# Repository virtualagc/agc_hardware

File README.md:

# AGC Hardware
This repository contains KiCAD projects and libraries for a replica of the Apollo Guidance Computer. The schematics have, for the most part, been digitized directly from [the original schematics](http://klabs.org/history/ech/agc_schematics/) for the computer. The schematics have been peppered with metadata required for digital simulation using my [agc\_simulation](https://github.com/thewonderidiot/agc_simulation) repository.

# Current Status
All logic modules (A1-A24) have been digitized and appear to be operating correctly in simulation. Additionally, one custom module, fixed\_erasable\_memory, has been designed. The simulation is able to completely pass the AGC Block Two Self-Check present in Aurora 12 (the only program we have so far with the complete version), so the central processor wiring is correct. Interfaces still need to be fully tested.

The current focus is on designing and building a working DSKY replica, which will make further interface testing significantly easier.

# Differences from the Real Thing
* Modern 74HC-series components are used due to the unavailability of RTL logic chips.
* I've taken advantage of the nearly-infinite fanout of 74HC chips to remove all fanout expansion gates.
* To reduce chip count, I've not limited myself to using only 3-input NOR gates; I also use NOT gates, 2-input NOR gates, and 4-input NOR gates, where applicable. Combined with the deletion of fanout expansion gates, the total chip count is roughly half of the original's.
* Again due to the nature of 74HC logic, outputs of NOR gates cannot be directly connected together as was possible with RTL. Where this is necessary (cross-module buses and >4 input gates), I've inserted fast open-drain buffers with accompanying pullup resistors. This gives very close to the same behavior, as the fan-in expander gates of the original were operating effectively open-collector lines.
* I've been fairly liberal about moving sections of logic around to make modules more stand-alone, and to condense related logic all into the same module. This facilited much easier development, and I anticipate it to make bench-testing individual modules easier when I've actually gotten boards manufactured. I also believe it to have significantly reduced the number of signals that will be going across the final backplane, although I have no numbers to back this up.
* The implementation for fixed and erasable memory module is custom, by me. It replaces all Tray B modules with the exception of the analog alarms module and the clock oscillator module.
* The implementation of the DSKY Indicator Driver module is the result of a joint reverse engineering effort between myself and Francois Rautenbach. It is based on several sources (R-700 volume III, Apollo 12 Mission Report, the CSM 104 Systems Handbook, the LM Systems Handbook, and the LM Primary Guidance Navigation and Control System Study Guide, among others). Thanks Francois!

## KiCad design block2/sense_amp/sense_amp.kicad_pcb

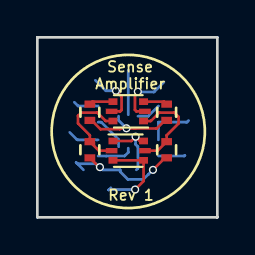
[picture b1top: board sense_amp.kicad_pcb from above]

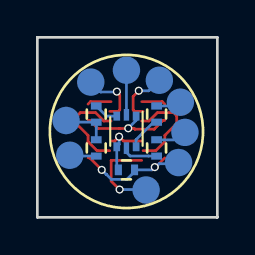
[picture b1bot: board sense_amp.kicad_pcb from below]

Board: 2 copper layers, 10.0 x 10.0 mm, 21 parts (15 on the bottom side), 18 nets.

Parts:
P1, P2, P3, P4, P6, P7, P8, P9, P10: CONN_01X01; Measurement_Point_Round-SMD-Pad_Small
Q1, Q3, Q5: DUAL_NPN_2; SOT-666
R1, R2, R7, R9: 5k; R_0402
R3, R4: 10; R_0402
R5, R6, R8: 250; R_0402

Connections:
unnamed: P1.1, Q5.3, Q5.4
unnamed: P2.1, Q1.2
unnamed: P3.1, R6.2
unnamed: P4.1, R5.2, R6.1
unnamed: P6.1, Q3.2
unnamed: P7.1, Q1.5
unnamed: P8.1, R8.2
unnamed: P9.1, R7.2
unnamed: P10.1, R1.1, R2.1, R9.1
unnamed: Q1.1, Q5.5, R1.2
unnamed: Q1.3, R3.1
unnamed: Q1.4, R4.1
unnamed: Q1.6, Q5.2, R2.2
unnamed: Q3.1, R3.2, R4.2
unnamed: Q3.3, R5.1
unnamed: Q3.4, Q5.1, Q5.6, R9.2
unnamed: Q3.5, R7.1
unnamed: Q3.6, R8.1

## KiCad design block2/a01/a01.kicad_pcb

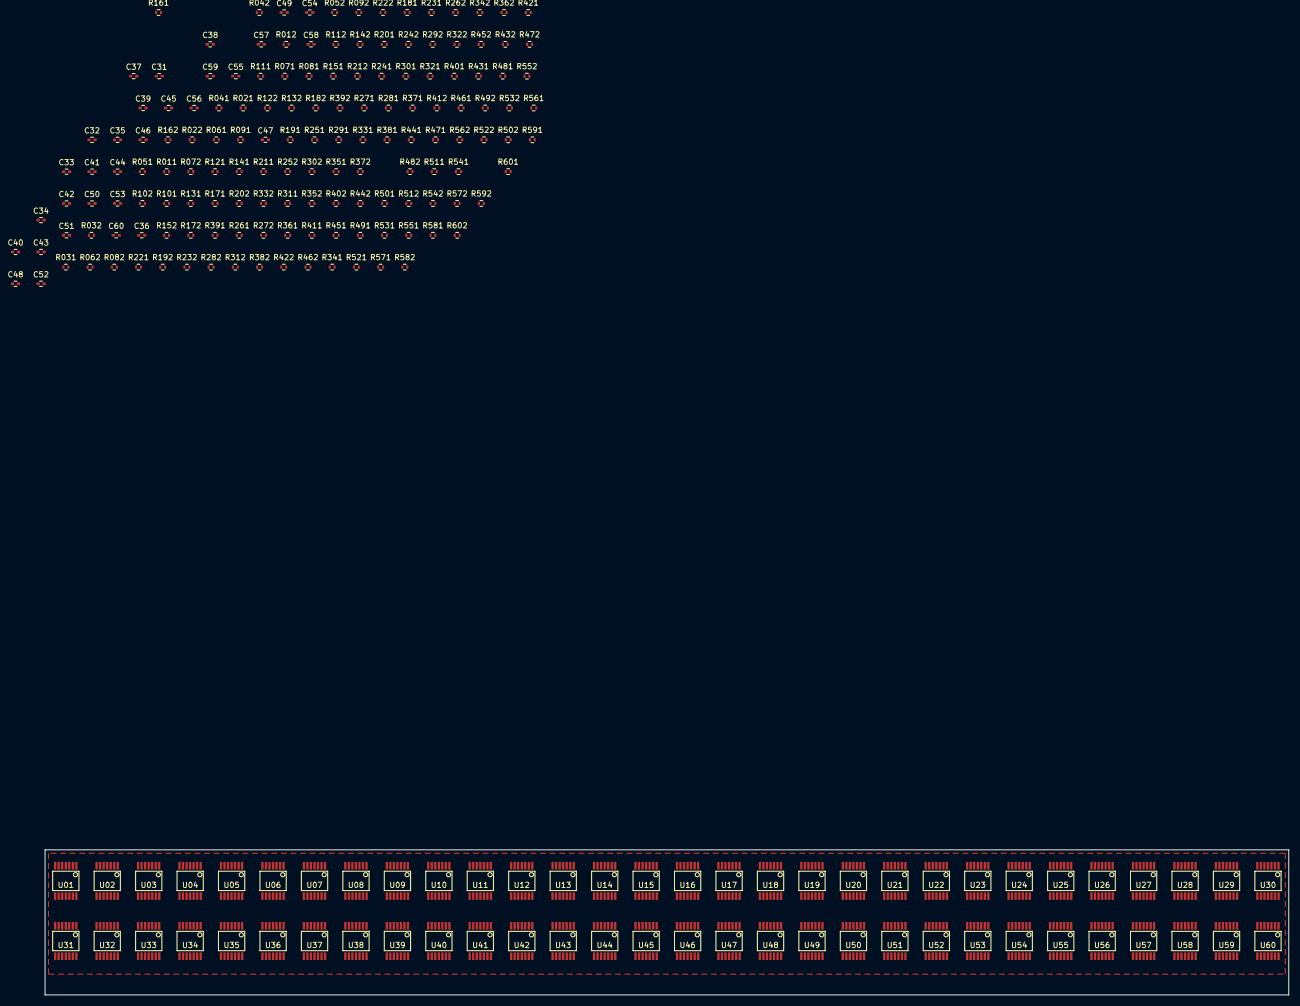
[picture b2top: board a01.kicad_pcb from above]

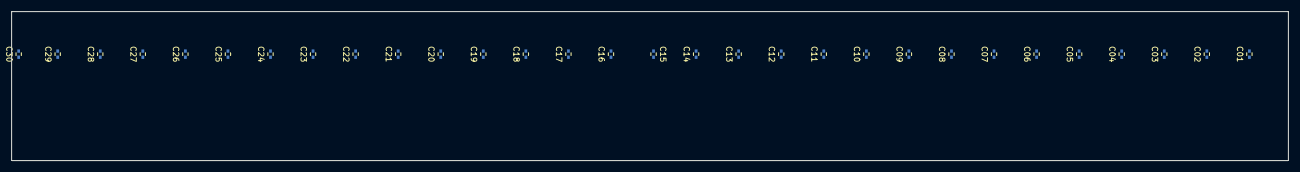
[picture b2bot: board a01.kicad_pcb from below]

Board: 2 copper layers, 228.6 x 26.7 mm, 240 parts (30 on the bottom side), 133 nets, no tracks yet.

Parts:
C01, C02, C03, C04, C05, C06, C07, C08, C09, C10, C11, C12, C13, C14, C15, C16, C17, C18, C19, C20, C21, C22, C23, C24, C25, C26, C27, C28, C29, C30, C31, C32, C33, C34, C35, C36, C37, C38, C39, C40, C41, C42, C43, C44, C45, C46, C47, C48, C49, C50, C51, C52, C53, C54, C55, C56, C57, C58, C59, C60: 0.1uF; C_0402
R011, R012, R021, R022, R031, R032, R041, R042, R051, R052, R061, R062, R071, R072, R081, R082, R091, R092, R101, R102, R111, R112, R121, R122, R131, R132, R141, R142, R151, R152, R161, R162, R171, R172, R181, R182, R191, R192, R201, R202, R211, R212, R221, R222, R231, R232, R241, R242, R251, R252, R261, R262, R271, R272, R281, R282, R291, R292, R301, R302, R311, R312, R321, R322, R331, R332, R341, R342, R351, R352, R361, R362, R371, R372, R381, R382, R391, R392, R401, R402, R411, R412, R421, R422, R431, R432, R441, R442, R451, R452, R461, R462, R471, R472, R481, R482, R491, R492, R501, R502, R511, R512, R521, R522, R531, R532, R541, R542, R551, R552, R561, R562, R571, R572, R581, R582, R591, R592, R601, R602: 3.3k; R_0402
U01, U02, U05, U06, U09, U13, U16, U20, U23, U27, U34, U35, U36, U38, U39, U41, U42, U43, U45, U48, U49, U52, U55, U56, U59, U60: 74HC05-B_C-E_F; SSOP-14
U03, U04, U07, U08, U18, U28, U29, U50, U54: 74HC05-ABC-E_F; SSOP-14
U10, U14, U17, U21: 74HC05-ACB-E_F; SSOP-14
U11, U15, U22, U46, U47, U51, U53, U57, U58: 74HC05-BAC-E_F; SSOP-14
U12, U19, U26: 74HC05-A_B-E_F; SSOP-14
U24: 74HC05-A_C-E_F; SSOP-14
U25, U44: 74HC05-ABC-DFE; SSOP-14
U30, U31: 74HC05-SPARE; SSOP-14
U32, U33: 74HC05-B_C-EDF; SSOP-14
U37, U40: 74HC05-BAC-DEF; SSOP-14

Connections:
0VDCA: C01.2, C02.2, C03.2, C04.2, C05.2, C06.2, C07.2, C08.2, C09.2, C10.2, C11.2, C12.2, C13.2, C14.2, C15.2, C16.2, C17.2, C18.2, C19.2, C20.2, C21.2, C22.2, C23.2, C24.2, C25.2, C26.2, C27.2, C28.2, C29.2, C30.2, C31.2, C32.2, C33.2, C34.2, C35.2, C36.2, C37.2, C38.2, C39.2, C40.2, C41.2, C42.2, C43.2, C44.2, C45.2, C46.2, C47.2, C48.2, C49.2, C50.2, C51.2, C52.2, C53.2, C54.2, C55.2, C56.2, C57.2, C58.2, C59.2, C60.2, U01.5, U01.7, U01.9, U02.5, U02.7, U02.9, U03.7, U03.9, U04.7, U04.9, U05.5, U05.7, U05.9, U06.5, U06.7, U06.9, U07.7, U07.9, U08.7, U08.9, U09.5, U09.7, U09.9, U10.7, U10.9, U11.7, U11.9, U12.1, U12.7, U12.9, U13.5, U13.7, U13.9, U14.7, U14.9, U15.7, U15.9, U16.5, U16.7, U16.9, U17.7, U17.9, U18.7, U18.9, U19.1, U19.7, U19.9, U20.5, U20.7, U20.9, U21.7, U21.9, U22.7, U22.9, U23.5, U23.7, U23.9, U24.3, U24.7, U24.9, U25.7, U26.1, U26.7, U26.9, U27.5, U27.7, U27.9, U28.7, U28.9, U29.7, U29.9, U30.1, U30.3, U30.5, U30.7, U30.9, U30.11, U30.13, U31.1, U31.3, U31.5, U31.7, U31.9, U31.11, U31.13, U32.5, U32.7, U33.5, U33.7, U34.5, U34.7, U34.9, U35.5, U35.7, U35.9, U36.5, U36.7, U36.9, U37.7, U38.5, U38.7, U38.9, U39.5, U39.7, U39.9, U40.7, U41.5, U41.7, U41.9, U42.5, U42.7, U42.9, U43.5, U43.7, U43.9, U44.7, U45.5, U45.7, U45.9, U46.7, U46.9, U47.7, U47.9, U48.5, U48.7, U48.9, U49.5, U49.7, U49.9, U50.7, U50.9, U51.7, U51.9, U52.5, U52.7, U52.9, U53.7, U53.9, U54.7, U54.9, U55.5, U55.7, U55.9, U56.5, U56.7, U56.9, U57.7, U57.9, U58.7, U58.9, U59.5, U59.7, U59.9, U60.5, U60.7, U60.9
+4VDC: R011.2, R012.2, R021.2, R022.2, R031.2, R032.2, R041.2, R042.2, R051.2, R052.2, R061.2, R062.2, R071.2, R072.2, R081.2, R082.2, R091.2, R092.2, R101.2, R102.2, R111.2, R112.2, R121.2, R122.2, R131.2, R132.2, R141.2, R142.2, R151.2, R152.2, R161.2, R162.2, R171.2, R172.2, R181.2, R182.2, R191.2, R192.2, R201.2, R202.2, R211.2, R212.2, R221.2, R222.2, R231.2, R232.2, R241.2, R242.2, R251.2, R252.2, R261.2, R262.2, R271.2, R272.2, R281.2, R282.2, R291.2, R292.2, R301.2, R302.2, R311.2, R312.2, R321.2, R322.2, R331.2, R332.2, R341.2, R342.2, R351.2, R352.2, R361.2, R362.2, R371.2, R372.2, R381.2, R382.2, R391.2, R392.2, R401.2, R402.2, R411.2, R412.2, R421.2, R422.2, R431.2, R432.2, R441.2, R442.2, R451.2, R452.2, R461.2, R462.2, R471.2, R472.2, R481.2, R482.2, R491.2, R492.2, R501.2, R502.2, R511.2, R512.2, R521.2, R522.2, R531.2, R532.2, R541.2, R542.2, R551.2, R552.2, R561.2, R562.2, R571.2, R572.2, R581.2, R582.2, R591.2, R592.2, R601.2, R602.2
FAP: C01.1, C02.1, C03.1, C04.1, C05.1, C06.1, C07.1, C08.1, C09.1, C10.1, C11.1, C12.1, C13.1, C14.1, C15.1, C16.1, C17.1, C18.1, C19.1, C20.1, C21.1, C22.1, C23.1, C24.1, C25.1, C26.1, C27.1, C28.1, C29.1, C30.1, C31.1, C32.1, C33.1, C34.1, C35.1, C36.1, C37.1, C38.1, C39.1, C40.1, C41.1, C42.1, C43.1, C44.1, C45.1, C46.1, C47.1, C48.1, C49.1, C50.1, C51.1, C52.1, C53.1, C54.1, C55.1, C56.1, C57.1, C58.1, C59.1, C60.1, U01.14, U02.14, U03.14, U04.14, U05.14, U06.14, U07.14, U08.14, U09.14, U10.14, U11.14, U12.14, U13.14, U14.14, U15.14, U16.14, U17.14, U18.14, U19.14, U20.14, U21.14, U22.14, U23.14, U24.14, U25.14, U26.14, U27.14, U28.14, U29.14, U30.14, U31.14, U32.14, U33.14, U34.14, U35.14, U36.14, U37.14, U38.14, U39.14, U40.14, U41.14, U42.14, U43.14, U44.14, U45.14, U46.14, U47.14, U48.14, U49.14, U50.14, U51.14, U52.14, U53.14, U54.14, U55.14, U56.14, U57.14, U58.14, U59.14, U60.14
unnamed: U28.3, U29.3
unnamed: U26.3, U26.13
unnamed: U55.11, U56.11
unnamed: U19.3, U19.13
unnamed: U48.13, U49.13
unnamed: U12.5, U12.11
unnamed: U42.3, U42.13
unnamed: U05.1, U07.13
unnamed: U32.9, U33.9
unnamed: U35.1, U35.11
U011: R011.1, U01.2, U01.4
U012: R012.1, U01.10, U01.12
U021: R021.1, U02.2, U02.4, U02.11, U04.13, U05.3
U022: R022.1, U02.3, U02.10, U02.12, U03.13
U031: R031.1, U02.13, U03.2, U03.4, U03.6, U03.11, U04.5
U032: R032.1, U03.1, U03.10, U03.12
U041: R041.1, U02.1, U03.5, U04.2, U04.4, U04.6, U04.11
U042: R042.1, U04.1, U04.10, U04.12
U051: R051.1, U05.2, U05.4
U052: R052.1, U05.10, U05.12, U06.11, U08.13
U061: R061.1, U03.3, U04.3, U06.2, U06.4, U07.5
U062: R062.1, U05.13, U06.1, U06.10, U06.12, U07.11
U071: R071.1, U06.3, U06.13, U07.2, U07.4, U07.6, U08.5
U072: R072.1, U07.10, U07.12
U081: R081.1, U05.11, U07.1, U08.2, U08.4, U08.6, U08.11
U082: R082.1, U08.1, U08.10, U08.12
U091: R091.1, U09.2, U09.4, U09.11, U10.11, U12.3
U092: R092.1, U09.3, U09.10, U09.12, U11.13
U101: R101.1, U09.1, U10.2, U10.4, U10.6, U10.13, U11.3
U102: R102.1, U07.3, U08.3, U10.5, U10.10, U10.12
U111: R111.1, U09.13, U10.3, U11.2, U11.4, U11.6, U11.11
U112: R112.1, U11.1, U11.10, U11.12
U121: R121.1, U12.4, U12.6
U122: R122.1, U12.10, U12.12
U131: R131.1, U12.13, U13.2, U13.4, U13.11, U14.11
U132: R132.1, U13.3, U13.10, U13.12, U15.13
U141: R141.1, U13.1, U14.2, U14.4, U14.6, U14.13, U15.3
U142: R142.1, U10.1, U11.5, U14.3, U14.10, U14.12
U151: R151.1, U13.13, U14.5, U15.2, U15.4, U15.6, U15.11
U152: R152.1, U15.1, U15.10, U15.12
U161: R161.1, U16.2, U16.4, U16.11, U17.11, U19.5
U162: R162.1, U16.3, U16.10, U16.12, U18.13
U171: R171.1, U16.1, U17.2, U17.4, U17.6, U17.13, U18.5
U172: R172.1, U14.1, U15.5, U17.5, U17.10, U17.12
U181: R181.1, U16.13, U17.3, U18.2, U18.4, U18.6, U18.11
U182: R182.1, U18.1, U18.10, U18.12
U191: R191.1, U19.4, U19.6
U192: R192.1, U19.10, U19.12
U201: R201.1, U19.11, U20.2, U20.4, U20.11, U21.11
U202: R202.1, U20.3, U20.10, U20.12, U22.13
U211: R211.1, U20.1, U21.2, U21.4, U21.6, U21.13, U22.3
U212: R212.1, U17.1, U18.3, U21.5, U21.10, U21.12
U221: R221.1, U20.13, U21.3, U22.2, U22.4, U22.6, U22.11
U222: R222.1, U22.1, U22.10, U22.12
U231: R231.1, U23.2, U23.4, U23.11, U24.5, U26.5
U232: R232.1, U23.3, U23.10, U23.12, U24.11
U241: R241.1, U21.1, U22.5, U24.2, U24.6, U25.5
U242: R242.1, U24.10, U24.12, U25.11
U251: R251.1, U23.1, U24.1, U25.2, U25.4, U25.6, U25.9
U252: R252.1, U23.13, U24.13, U25.1, U25.8, U25.10, U25.12
U261: R261.1, U26.4, U26.6
U262: R262.1, U26.10, U26.12
U271: R271.1, U26.11, U27.2, U27.4, U27.11, U28.11
U272: R272.1, U27.3, U27.10, U27.12, U29.13
U281: R281.1, U27.1, U28.2, U28.4, U28.6, U28.13, U29.5
U282: R282.1, U25.3, U25.13, U28.5, U28.10, U28.12
U291: R291.1, U27.13, U28.1, U29.2, U29.4, U29.6, U29.11
U292: R292.1, U29.1, U29.10, U29.12
U301: R301.1, U30.2, U30.4, U30.6
U302: R302.1, U30.8, U30.10, U30.12
U311: R311.1, U31.2, U31.4, U31.6
U312: R312.1, U31.8, U31.10, U31.12
U321: R321.1, U32.2, U32.4, U32.11, U37.5, U37.11
U322: R322.1, U32.1, U32.8, U32.10, U32.12, U33.11, U34.3
U331: R331.1, U33.2, U33.4, U33.13
U332: R332.1, U32.13, U33.1, U33.8, U33.10, U33.12, U34.11
U341: R341.1, U32.3, U34.2, U34.4, U34.13, U35.3
U342: R342.1, U33.3, U34.1, U34.10, U34.12
U351: R351.1, U35.2, U35.4
U352: R352.1, U35.10, U35.12
U361: R361.1, U36.2, U36.4, U37.3
U362: R362.1, U36.10, U36.12, U37.9, U40.5, U40.11
U371: R371.1, U36.1, U37.2, U37.4, U37.6, U37.13, U38.11
U372: R372.1, U36.13, U37.1, U37.8, U37.10, U37.12, U38.3
U381: R381.1, U35.13, U36.11, U38.2, U38.4, U38.13
U382: R382.1, U36.3, U38.1, U38.10, U38.12
U391: R391.1, U39.2, U39.4, U40.3, U44.3, U44.13
U392: R392.1, U39.10, U39.12, U40.9
U401: R401.1, U39.1, U40.2, U40.4, U40.6, U40.13, U41.3
U402: R402.1, U39.13, U40.1, U40.8, U40.10, U40.12, U41.11
U411: R411.1, U39.3, U41.2, U41.4, U41.13, U42.1
U412: R412.1, U39.11, U41.1, U41.10, U41.12
U421: R421.1, U42.2, U42.4
U422: R422.1, U42.10, U42.12
U431: R431.1, U43.2, U43.4, U44.5
U432: R432.1, U43.10, U43.12, U44.9, U46.5, U47.5
U441: R441.1, U43.1, U44.2, U44.4, U44.6, U44.11, U45.3
U442: R442.1, U43.13, U44.1, U44.8, U44.10, U44.12, U45.11
U451: R451.1, U43.3, U45.2, U45.4, U45.13
U452: R452.1, U42.11, U43.11, U45.1, U45.10, U45.12
U461: R461.1, U46.2, U46.4, U46.6, U46.13, U47.3, U49.1
U462: R462.1, U46.1, U46.10, U46.12
U471: R471.1, U46.3, U47.2, U47.4, U47.6, U47.11, U48.3
U472: R472.1, U47.1, U47.10, U47.12, U50.3, U51.5
U481: R481.1, U47.13, U48.2, U48.4, U48.11, U49.3
U482: R482.1, U48.10, U48.12
U491: R491.1, U46.11, U48.1, U49.2, U49.4
U492: R492.1, U49.10, U49.12
U501: R501.1, U50.2, U50.4, U50.6, U50.13, U51.3, U52.3
U502: R502.1, U50.5, U50.10, U50.12
U511: R511.1, U50.1, U51.2, U51.4, U51.6, U51.13, U52.11
U512: R512.1, U51.1, U51.10, U51.12, U53.5, U54.3
U521: R521.1, U50.11, U52.2, U52.4, U52.13
U522: R522.1, U49.11, U51.11, U52.1, U52.10, U52.12
U531: R531.1, U53.2, U53.4, U53.6, U53.13, U54.5, U56.1
U532: R532.1, U53.1, U53.10, U53.12
U541: R541.1, U53.3, U54.2, U54.4, U54.6, U54.11, U55.3
U542: R542.1, U54.1, U54.10, U54.12, U57.5, U58.5
U551: R551.1, U54.13, U55.2, U55.4, U55.13, U56.3
U552: R552.1, U55.10, U55.12
U561: R561.1, U53.11, U55.1, U56.2, U56.4
U562: R562.1, U56.10, U56.12
U571: R571.1, U57.2, U57.4, U57.6, U57.13, U58.1, U59.13
U572: R572.1, U57.1, U57.10, U57.12
U581: R581.1, U57.3, U58.2, U58.4, U58.6, U58.11, U59.3
U582: R582.1, U58.3, U58.10, U58.12
U591: R591.1, U58.13, U59.2, U59.4, U59.11
U592: R592.1, U56.13, U57.11, U59.1, U59.10, U59.12
U601: R601.1, U60.2, U60.4
U602: R602.1, U60.10, U60.12

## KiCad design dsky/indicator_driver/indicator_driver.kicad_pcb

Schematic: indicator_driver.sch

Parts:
C1, C2: 4.7uF
C3, C4, C5, C6, C7: 0.1uF
CR1, CR2, CR3, CR4, CR5, CR6, CR7, CR8, CR9, CR10, CR11, CR12, CR13, CR14, CR15, CR16, CR17, CR18, CR19, CR20, CR21, CR22, CR23, CR24, CR25, CR26, CR27, CR28, CR29, CR30, CR31, CR32, CR33, CR34, CR35, CR36, CR37, CR38, CR39, CR40, CR41, CR42, CR43, CR44, CR45, CR46, CR47, CR48, CR49, CR50, CR51, CR52, CR53, CR54, CR55, CR56, CR57, CR58, CR59, CR60, CR61, CR62, CR63, CR64: D
K1, K2, K3, K4, K5, K6, K7, K8, K9, K10, K11, K12, K13, K14, K15, K16, K17, K18, K19, K20: EC2-12TNU
K21, K22: EC2-12NU
L1, L2: 8.2uH
P1: PCN10A-128P
Q1, Q8, Q9, Q10, Q11, Q12, Q13: PN2907A
Q2, Q3, Q4, Q5, Q6, Q7: PN2222A
R1, R2, R3, R4, R6, R7, R9, R11, R12, R15, R16, R19, R22, R24: 10k
R5, R8, R10: 18k
R13, R17: 20k
R14, R18, R21, R23: 2k
R20, R25: 1k
R101, R102, R103, R104, R105, R106, R107, R108, R109, R110, R111, R112, R113, R114, R115, R116, R117, R118, R119, R120, R121, R122, R123, R124, R125, R126, R127, R128, R129, R130, R131, R132, R133, R134, R135, R136, R137, R138, R139, R140, R141, R142: 1.5k

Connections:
+28VDC: L1.1, P1.112
GND: C1.2, C2.2, CR47.2 (A), CR48.2 (A), CR49.2 (A), CR50.2 (A), P1.68, P1.105, Q2.1, Q3.1, Q5.1, Q7.1, R4.2, R7.2, R9.2, R11.2, R20.2, R25.2
unnamed: C1.1, L1.2, L2.1
unnamed: C2.1, C3.1, C4.1, C5.1, C6.1, C7.1, CR43.1 (K), CR45.1 (K), L2.2, Q1.1, Q8.1, Q9.1, Q10.1, Q11.1, Q12.1, Q13.1, R2.1, R3.1, R14.1, R15.1, R18.1, R19.1, R21.1, R23.1
unnamed: C3.2, Q1.2, R1.1, R2.2
unnamed: C4.2, Q8.2, R12.1, R14.2
unnamed: C5.2, Q10.2, R16.1, R18.2
unnamed: C6.2, Q12.2, R21.2, R22.1
unnamed: C7.2, Q13.2, R23.2, R24.1
unnamed: CR1.2 (A), K1.12
unnamed: CR2.2 (A), K1.7
unnamed: CR3.2 (A), K2.12
unnamed: CR4.2 (A), K2.7
unnamed: CR5.2 (A), K3.12
unnamed: CR6.2 (A), K3.7
unnamed: CR7.2 (A), K4.12
unnamed: CR8.2 (A), K4.7
unnamed: CR9.2 (A), K5.12
unnamed: CR10.2 (A), K5.7
unnamed: CR11.2 (A), K6.12
unnamed: CR12.2 (A), K6.7
unnamed: CR13.2 (A), K7.12
unnamed: CR14.2 (A), K7.7
unnamed: CR15.2 (A), K8.12
unnamed: CR16.2 (A), K8.7
unnamed: CR17.2 (A), K9.12
unnamed: CR18.2 (A), K9.7
unnamed: CR19.2 (A), K10.12
unnamed: CR20.2 (A), K10.7
unnamed: CR21.2 (A), K11.12
unnamed: CR22.2 (A), K11.7
unnamed: CR23.2 (A), K12.12
unnamed: CR24.2 (A), K12.7
unnamed: CR25.2 (A), K13.12
unnamed: CR26.2 (A), K13.7
unnamed: CR27.2 (A), K14.12
unnamed: CR28.2 (A), K14.7
unnamed: CR29.2 (A), K15.12
unnamed: CR30.2 (A), K15.7
unnamed: CR31.2 (A), K16.12
unnamed: CR32.2 (A), K16.7
unnamed: CR33.2 (A), K17.12
unnamed: CR34.2 (A), K17.7
unnamed: CR35.2 (A), K18.12
unnamed: CR36.2 (A), K18.7
unnamed: CR37.2 (A), K19.12
unnamed: CR38.2 (A), K19.7
unnamed: CR39.2 (A), K20.12
unnamed: CR40.2 (A), K20.7
unnamed: CR44.1 (K), Q4.2, R9.1
unnamed: CR46.1 (K), Q6.2, R11.1
unnamed: CR59.1 (K), CR60.1 (K), CR61.1 (K), CR62.1 (K), CR63.1 (K), CR64.1 (K), Q3.3
unnamed: K1.1, R101.1
unnamed: K1.6, R102.2
unnamed: K2.1, R103.1
unnamed: K2.6, R104.2
unnamed: K3.1, R105.1
unnamed: K3.4, K5.3
unnamed: K3.6, R106.2
unnamed: K4.1, R107.1
unnamed: K4.6, R108.2
unnamed: K5.1, R109.1
unnamed: K5.6, R110.2
unnamed: K6.1, R111.1
unnamed: K6.6, R112.2
unnamed: K7.1, R113.1
unnamed: K7.6, R114.2
unnamed: K8.1, R115.1
unnamed: K8.6, R116.2
unnamed: K9.1, R117.1
unnamed: K9.6, R118.2
unnamed: K10.1, R119.1
unnamed: K8.4, K10.3
unnamed: K10.6, R120.2
unnamed: K11.1, R121.1
unnamed: K11.6, R122.2
unnamed: K12.1, R123.1
unnamed: K12.6, R124.2
unnamed: K13.1, R125.1
unnamed: K13.4, K15.3
unnamed: K13.6, R126.2
unnamed: K14.1, R127.1
unnamed: K14.6, R128.2
unnamed: K15.1, R129.1
unnamed: K15.6, R130.2
unnamed: K16.1, R131.1
unnamed: K16.6, R132.2
unnamed: K17.1, R133.1
unnamed: K17.6, R134.2
unnamed: K18.1, R135.1
unnamed: K18.6, R136.2
unnamed: K19.1, R137.1
unnamed: K19.6, R138.2
unnamed: K20.1, R139.1
unnamed: K20.6, R140.2
unnamed: K21.12, R141.2
unnamed: K22.12, R142.2
unnamed: Q3.2, R6.1, R7.1
unnamed: Q4.1, Q5.2, R25.1
unnamed: Q6.1, Q7.2, R20.1
unnamed: Q9.2, R13.1, R15.2
unnamed: Q11.2, R17.1, R19.2
P1: K21.5, P1.1
P2: K21.10, P1.2
P3: K22.5, P1.3
P4: CR42.1 (K), K22.1, P1.4
P5: K22.3, P1.5
P6: K22.4, P1.6
P7: CR41.1 (K), K21.1, P1.7
P8: K21.9, P1.8
P9: K16.10, K17.10, P1.9
P10: K21.8, P1.10
P11: K21.4, P1.11
P12: K21.3, P1.12
P13: K11.10, K12.10, K13.3, K13.10, K14.10, K15.10, K19.10, K20.3, K20.10, P1.13
P14: P1.14, R102.1, R112.1, R122.1
P15: K16.5, P1.15
P16: K1.10, K2.10, K3.3, K3.10, K4.10, K5.10, K6.10, K7.10, K8.3, K8.10, K9.10, K10.10, P1.16
P17: K11.9, P1.17
P18: K16.9, P1.18
P19: P1.19, R132.1
P20: K16.3, P1.20
P21: K16.4, P1.21
P22: K1.9, P1.22
P23: P1.23, R101.2, R111.2, R121.2
P24: K6.9, P1.24
P25: K17.5, P1.25
P26: CR41.2 (A), CR42.2 (A), P1.26, R141.1, R142.1
P27: K16.8, P1.27
P28: P1.28, R131.2
P29: K12.5, K15.9, P1.29
P30: K2.5, K5.9, P1.30
P31: K17.3, P1.31
P32: K1.8, K2.3, K3.8, K4.8, K5.5, K5.8, K6.8, K7.3, K8.8, K9.8, K10.5, K10.8, K11.8, K12.3, K13.8, K14.8, K15.5, K15.8, K19.5, K19.8, K20.8, P1.32
P33: P1.33, R134.1
P34: K12.9, P1.34
P35: P1.35, R104.1, R114.1, R124.1
P36: K7.5, K10.9, P1.36
P37: K17.4, P1.37
P38: K17.9, P1.38
P39: K2.9, P1.39
P40: K7.9, P1.40
P41: K2.4, P1.41
P42: K7.4, P1.42
P43: K12.4, P1.43
P44: P1.44, R103.2, R113.2, R123.2
P45: K18.3, P1.45
P46: K18.5, P1.46
P47: CR31.1 (K), CR32.1 (K), CR33.1 (K), CR34.1 (K), CR35.1 (K), CR36.1 (K), P1.47
P48: P1.48, R133.2
P49: K8.5, K9.9, P1.49
P50: K13.5, K14.9, P1.50
P51: P1.51, R106.1, R116.1, R126.1
P52: P1.52, R136.1
P53: K12.8, K13.9, P1.53
P54: K7.8, K8.9, P1.54
P55: K2.8, K3.9, P1.55
P56: K3.5, K4.9, P1.56
P57: K17.8, K18.8, P1.57
P58: K18.4, P1.58
P59: P1.59, R135.2
P60: K18.9, P1.60
P61: P1.61, R108.1, R118.1, R128.1
P62: P1.62, R105.2, R115.2, R125.2
P63: K19.3, P1.63
P64: K18.10, P1.64
P65: P1.65, R107.2, R117.2, R127.2
P66: CR11.1 (K), CR12.1 (K), CR13.1 (K), CR14.1 (K), CR15.1 (K), CR16.1 (K), CR17.1 (K), CR18.1 (K), CR19.1 (K), CR20.1 (K), P1.66
P67: CR21.1 (K), CR22.1 (K), CR23.1 (K), CR24.1 (K), CR25.1 (K), CR26.1 (K), CR27.1 (K), CR28.1 (K), CR29.1 (K), CR30.1 (K), P1.67
P69: CR37.1 (K), CR38.1 (K), P1.69
P70: K19.9, P1.70
P71: CR1.1 (K), CR2.1 (K), CR3.1 (K), CR4.1 (K), CR5.1 (K), CR6.1 (K), CR7.1 (K), CR8.1 (K), CR9.1 (K), CR10.1 (K), P1.71
P72: P1.72, R138.1
P73: P1.73, R110.1, R120.1, R130.1
P74: K20.5, P1.74
P75: P1.75, R137.2
P76: K19.4, P1.76
P77: P1.77, R109.2, R119.2, R129.2
P78: K15.4, P1.78
P79: K20.9, P1.79
P80: P1.80, R140.1
P81: P1.81, R139.2
P82: K20.4, P1.82
P83: K5.4, P1.83
P84: K10.4, P1.84
P85: P1.85, R22.2
P86: P1.86, R24.2
P87: P1.87, Q12.3
P88: CR39.1 (K), CR40.1 (K), P1.88
P89: P1.89, R16.2
P90: P1.90, R12.2
P91: P1.91, R1.2
P92: P1.92, Q1.3
P94: CR57.2 (A), P1.94
P95: P1.95, Q13.3
P97: CR53.2 (A), P1.97
P98: CR54.2 (A), P1.98
P99: CR55.2 (A), P1.99
P100: CR56.2 (A), P1.100
P101: CR49.1 (K), P1.101, Q11.3
P102: CR47.1 (K), P1.102, Q9.3
P103: CR50.1 (K), P1.103, Q10.3, R17.2
P104: CR48.1 (K), P1.104, Q8.3, R13.2
P106: CR46.2 (A), P1.106, R10.2
P107: CR44.2 (A), R8.2
P108: CR52.2 (A), P1.108
P109: CR60.2 (A), P1.109
P110: CR51.2 (A), P1.110
P111: CR51.1 (K), CR52.1 (K), CR53.1 (K), CR54.1 (K), CR55.1 (K), CR56.1 (K), CR57.1 (K), P1.111, Q2.3, R3.2, R6.2
P113: CR45.2 (A), P1.113, Q6.3, Q7.3
P114: CR43.2 (A), P1.114, Q4.3, Q5.3
P115: P1.115, R5.2
P116: CR59.2 (A), P1.116
P117: CR62.2 (A), P1.117
P118: CR61.2 (A), P1.118
P119: P1.119, Q2.2, R4.1, R5.1
P120: P1.120, R8.1, R10.1
P121: CR58.1 (K), P1.121
P122: CR64.2 (A), P1.122
P123: CR58.2 (A), P1.123
P124: CR63.2 (A), P1.124

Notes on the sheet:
CKT 000
CKT 001
CKT 002
CKT 003
CKT 004
CKT 005
CKT 006
CKT 007
CKT 008
CKT 009
CKT 011
EV250
OSGRD
0VDC

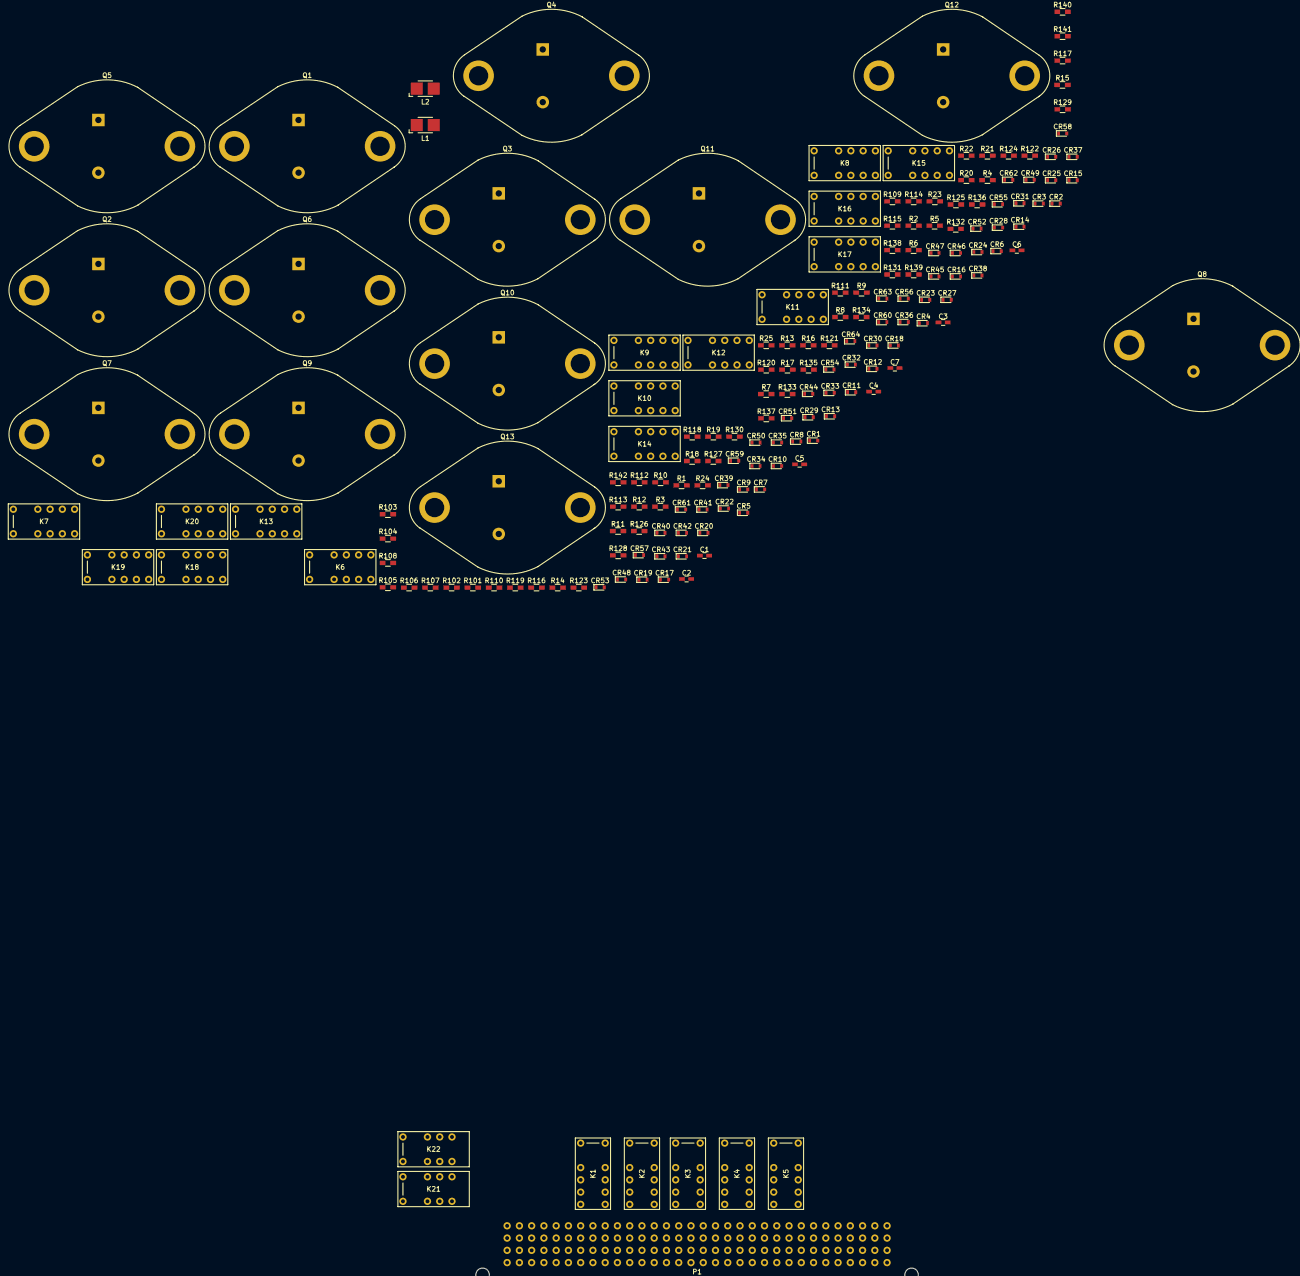
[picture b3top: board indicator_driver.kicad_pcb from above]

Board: 2 copper layers, 176 parts (0 on the bottom side), 221 nets, no tracks yet.

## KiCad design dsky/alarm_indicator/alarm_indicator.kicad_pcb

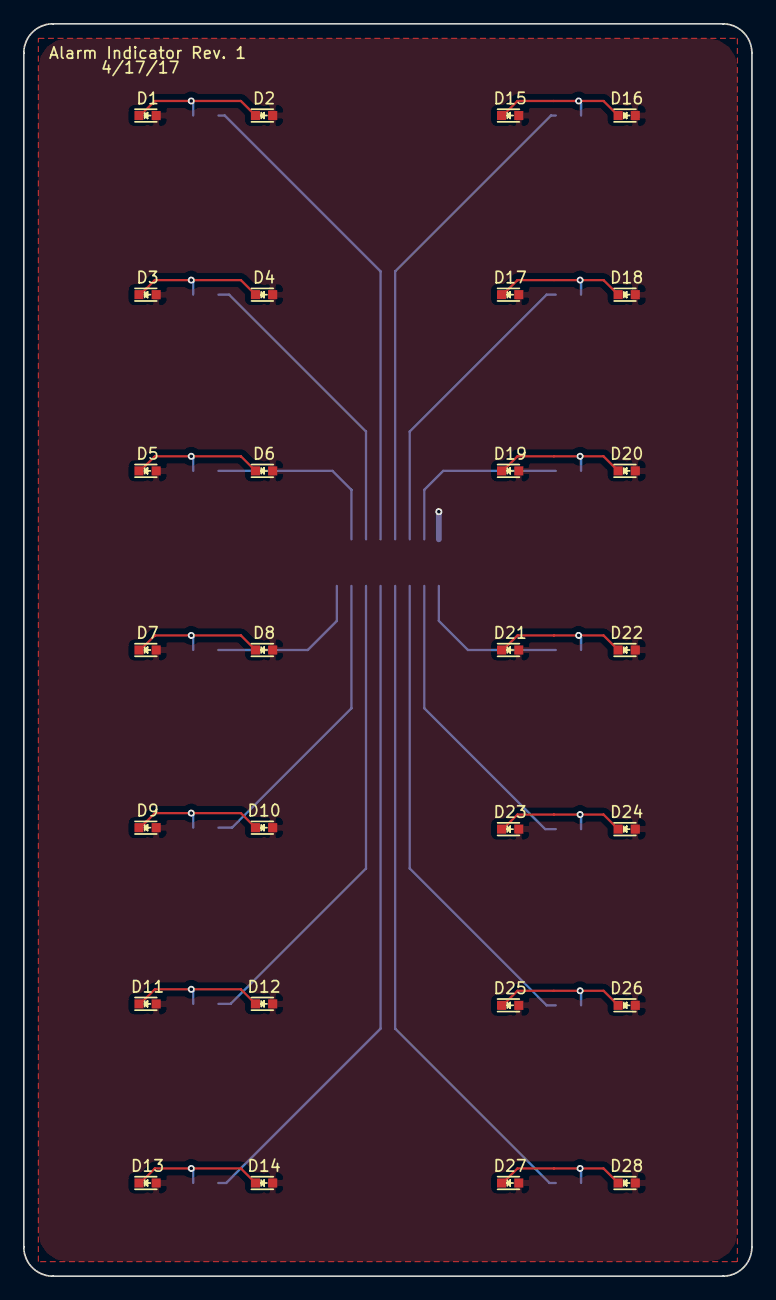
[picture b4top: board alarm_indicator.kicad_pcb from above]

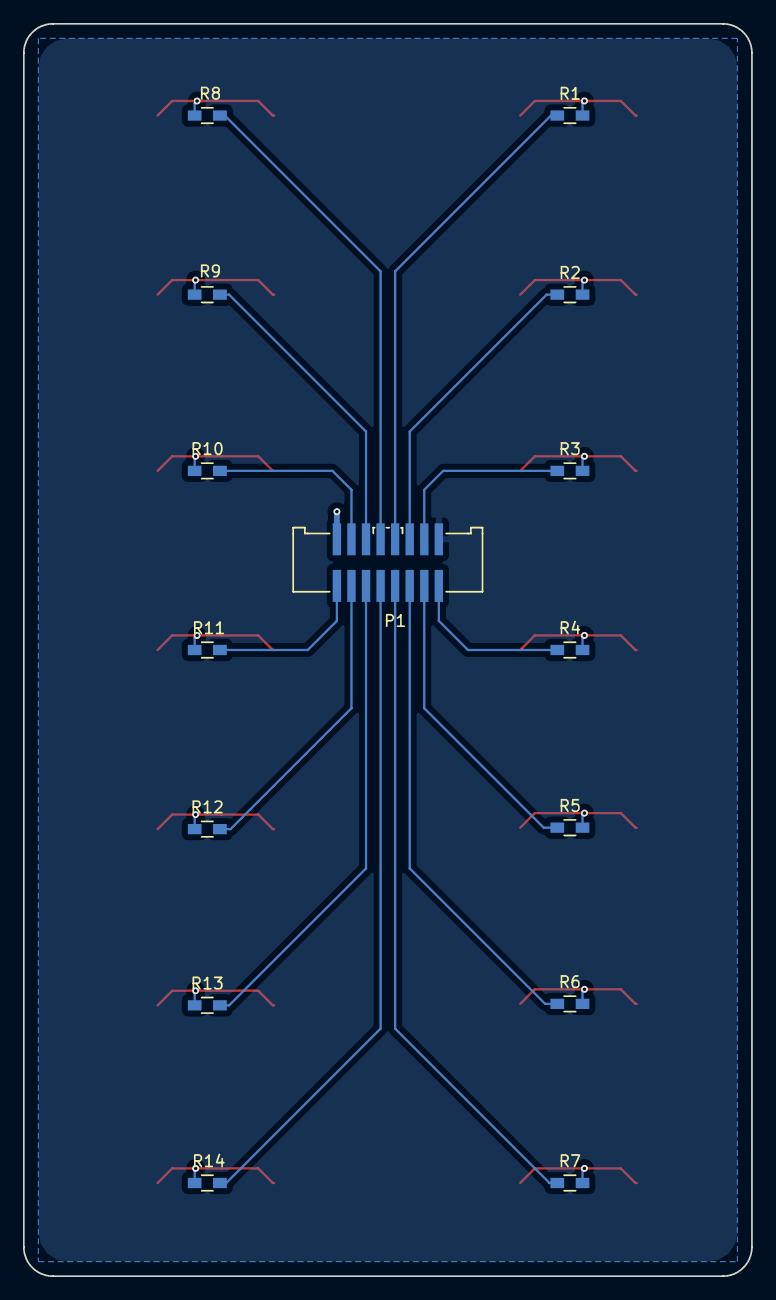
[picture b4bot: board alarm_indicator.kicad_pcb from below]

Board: 2 copper layers, 63.5 x 109.2 mm, 43 parts (15 on the bottom side), 29 nets.

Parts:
D1, D2, D3, D4, D5, D6, D7, D8, D9, D10, D11, D12, D13, D14, D15, D16, D17, D18, D19, D20, D21, D22, D23, D24, D25, D26, D27, D28: LED; LED-0603
P1: CONN_02X08; SHF-108-01-L-D-SM
R1, R2, R3, R4, R5, R6, R7, R8, R9, R10, R11, R12, R13, R14: 500; R_0603_HandSoldering

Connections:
+12V: D1.2, D2.2, D3.2, D4.2, D5.2, D6.2, D7.2, D8.2, D9.2, D10.2, D11.2, D12.2, D13.2, D14.2, D15.2, D16.2, D17.2, D18.2, D19.2, D20.2, D21.2, D22.2, D23.2, D24.2, D25.2, D26.2, D27.2, D28.2, P1.2
ALT: P1.5, R13.1
GIMBAL_LOCK: P1.6, R9.1
KEY_REL: P1.15, R4.1
NO_ATT: P1.12, R2.1
NO_DAP: P1.9, R7.1
unnamed: D1.1, D2.1, R1.2
unnamed: D3.1, D4.1, R2.2
unnamed: D5.1, D6.1, R3.2
unnamed: D7.1, D8.1, R4.2
unnamed: D9.1, D10.1, R5.2
unnamed: D11.1, D12.1, R6.2
unnamed: D13.1, D14.1, R7.2
unnamed: D15.1, D16.1, R8.2
unnamed: D17.1, D18.1, R9.2
unnamed: D19.1, D20.1, R10.2
unnamed: D21.1, D22.1, R11.2
unnamed: D23.1, D24.1, R12.2
unnamed: D25.1, D26.1, R13.2
unnamed: D27.1, D28.1, R14.2
OPR_ERR: P1.13, R5.1
PRIO_DISP: P1.11, R6.1
PROG: P1.4, R10.1
RESTART: P1.1, R11.1
STBY: P1.14, R3.1
TEMP: P1.8, R8.1
TRACKER: P1.3, R12.1
UPLINK_ACTY: P1.10, R1.1
VEL: P1.7, R14.1
